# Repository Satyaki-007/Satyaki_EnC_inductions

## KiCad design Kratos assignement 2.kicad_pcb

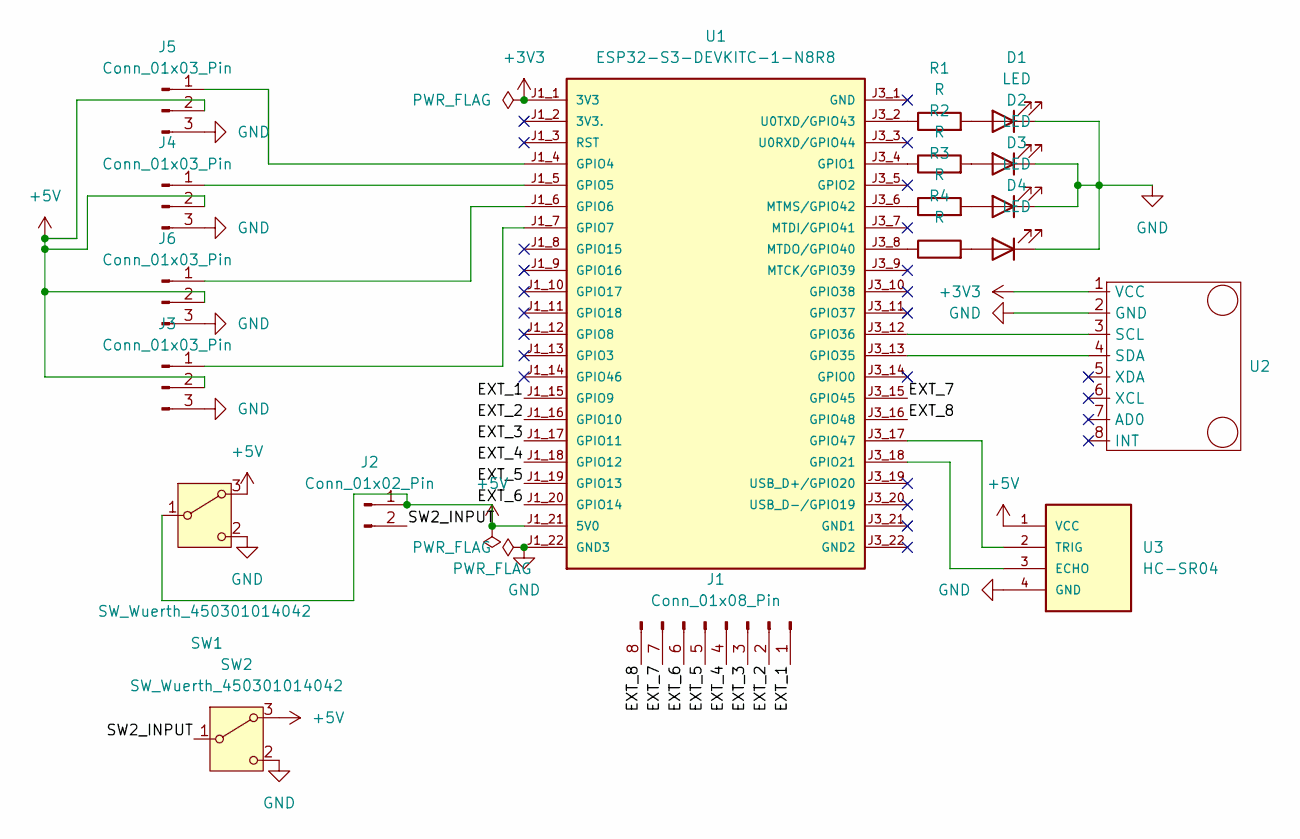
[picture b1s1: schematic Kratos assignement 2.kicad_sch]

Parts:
D1, D2, D3, D4: LED; LED_D5.0mm
J1: Conn_01x08_Pin; PinHeader_1x08_P2.54mm_Vertical
J2: Conn_01x02_Pin; PinHeader_1x02_P2.54mm_Vertical
J3, J4, J5, J6: Conn_01x03_Pin; PinHeader_1x03_P2.54mm_Vertical
R1, R2, R3, R4: R; R_Axial_DIN0207_L6.3mm_D2.5mm_P10.16mm_Horizontal
SW1, SW2: SW_Wuerth_450301014042; SW_Slide-03_Wuerth-WS-SLTV_10x2.5x6.4_P2.54mm
U1: ESP32-S3-DEVKITC-1-N8R8
U2: PinSocket_1x08_P2.54mm_Vertical
U3: HC-SR04; XCVR_HC-SR04

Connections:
+3V3: U1.J1_1 (3V3), U2.1 (VCC)
+5V: J2.1, J3.2, J4.2, J5.2, J6.2, SW1.1 (B), SW1.3 (A), SW2.3 (A), U1.J1_21 (5V0), U3.1 (VCC)
/EXT_1: J1.1, U1.J1_15 (GPIO9)
/EXT_2: J1.2, U1.J1_16 (GPIO10)
/EXT_3: J1.3, U1.J1_17 (GPIO11)
/EXT_4: J1.4, U1.J1_18 (GPIO12)
/EXT_5: J1.5, U1.J1_19 (GPIO13)
/EXT_6: J1.6, U1.J1_20 (GPIO14)
/EXT_7: J1.7, U1.J3_15 (GPIO45)
/EXT_8: J1.8, U1.J3_16 (GPIO48)
/SW2_INPUT: J2.2, SW2.1 (B)
GND: D1.1 (K), D2.1 (K), D3.1 (K), D4.1 (K), J3.3, J4.3, J5.3, J6.3, SW1.2 (C), SW2.2 (C), U1.J1_22 (GND3), U2.2 (GND), U3.4 (GND)
unnamed: D1.2 (A), R1.2
unnamed: D2.2 (A), R2.2
unnamed: D3.2 (A), R3.2
unnamed: D4.2 (A), R4.2
unnamed: J3.1, U1.J1_7 (GPIO7)
unnamed: J4.1, U1.J1_5 (GPIO5)
unnamed: J5.1, U1.J1_4 (GPIO4)
unnamed: J6.1, U1.J1_6 (GPIO6)
unnamed: R2.1, U1.J3_4 (GPIO1)
unnamed: U1.J3_18 (GPIO21), U3.3 (ECHO)
unnamed: U1.J3_13 (GPIO35), U2.4 (SDA)
unnamed: U1.J3_12 (GPIO36), U2.3 (SCL)
unnamed: U1.J3_17 (GPIO47), U3.2 (TRIG)
unnamed: R4.1, U1.J3_8 (MTDO/GPIO40)
unnamed: R3.1, U1.J3_6 (MTMS/GPIO42)
unnamed: R1.1, U1.J3_2 (U0TXD/GPIO43)

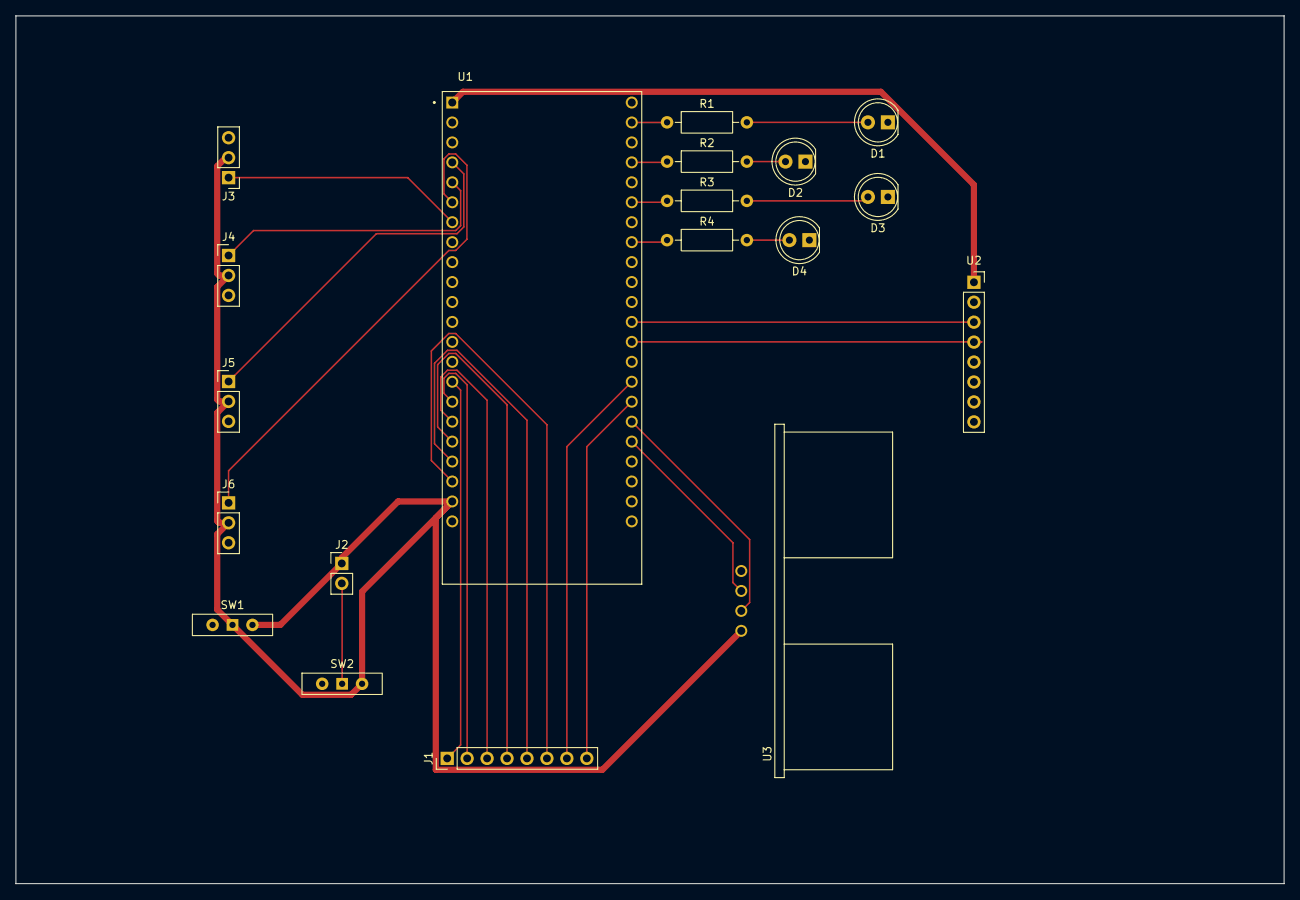
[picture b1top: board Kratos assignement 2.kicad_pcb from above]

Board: 2 copper layers, 161.5 x 110.5 mm, 19 parts (0 on the bottom side), 28 nets.
